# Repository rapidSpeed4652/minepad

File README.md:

# MinePad
Minepad is a 4 key macropad with a rotary encoder. It uses VIAL, which is a fork of QMK firmware.

(If it looks very green, try disabling the Edge.Cuts layer from the layers tab)

## Features
- 4 Cherry-MX keys
- 1 knob
- Support for mapping the keys and knob using VIAL

## CAD Model
It has two main parts and 8 small parts making the title and the logo. Made in Onshape!

## Schematic and PCB
Here's my schematic! Made in KiCAD.

PCB!

## Firmware
I have used VIAL, a fork of QMK firmware, to make it possible to map keys using a web portal.
- Rotary encoder for volume
- One key for pause/play
- Another for mute

I will decide what I do with other keys later.

## BOM
Everything needed to make this macropad:
- 4x Cherry MX Switches
- 1x EC11 Rotary Encoder
- 4x 1u Keycaps
- 1x Seeed XIAO RP2040
- 1x Case (All printed parts)

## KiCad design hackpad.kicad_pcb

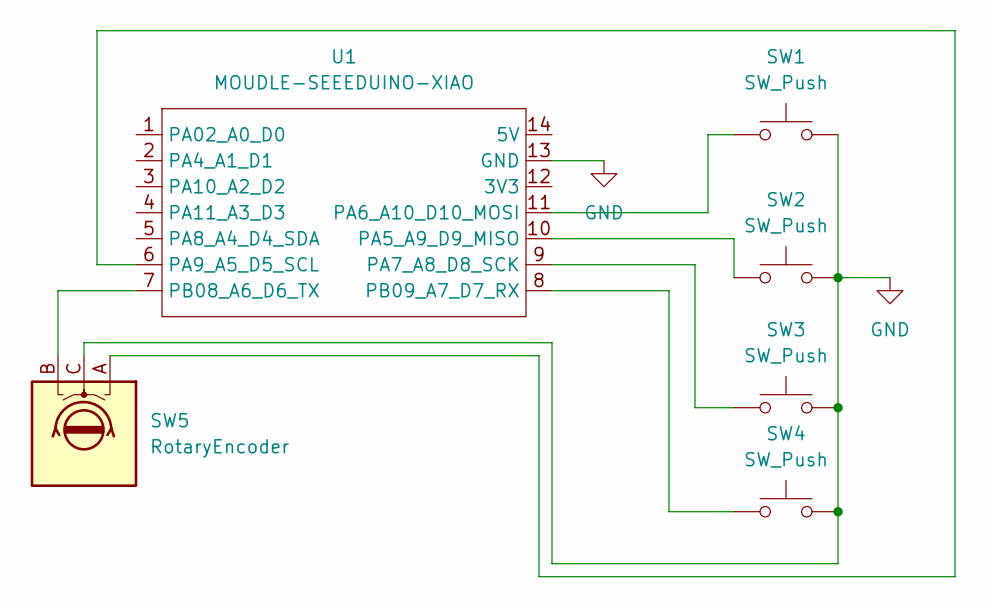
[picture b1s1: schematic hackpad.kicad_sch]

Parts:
SW1, SW2, SW3, SW4: SW_Push; SW_Cherry_MX_1.00u_PCB
SW5: RotaryEncoder; RotaryEncoder_Alps_EC12E-Switch_Vertical_H20mm
U1: MOUDLE-SEEEDUINO-XIAO; MCU_Seeed_ESP32C3

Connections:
GND: SW1.2, SW2.2, SW3.2, SW4.2, SW5.C, U1.13 (GND)
unnamed: SW2.1, U1.10 (PA5_A9_D9_MISO)
unnamed: SW1.1, U1.11 (PA6_A10_D10_MOSI)
unnamed: SW3.1, U1.9 (PA7_A8_D8_SCK)
unnamed: SW5.A, U1.6 (PA9_A5_D5_SCL)
unnamed: SW5.B, U1.7 (PB08_A6_D6_TX)
unnamed: SW4.1, U1.8 (PB09_A7_D7_RX)

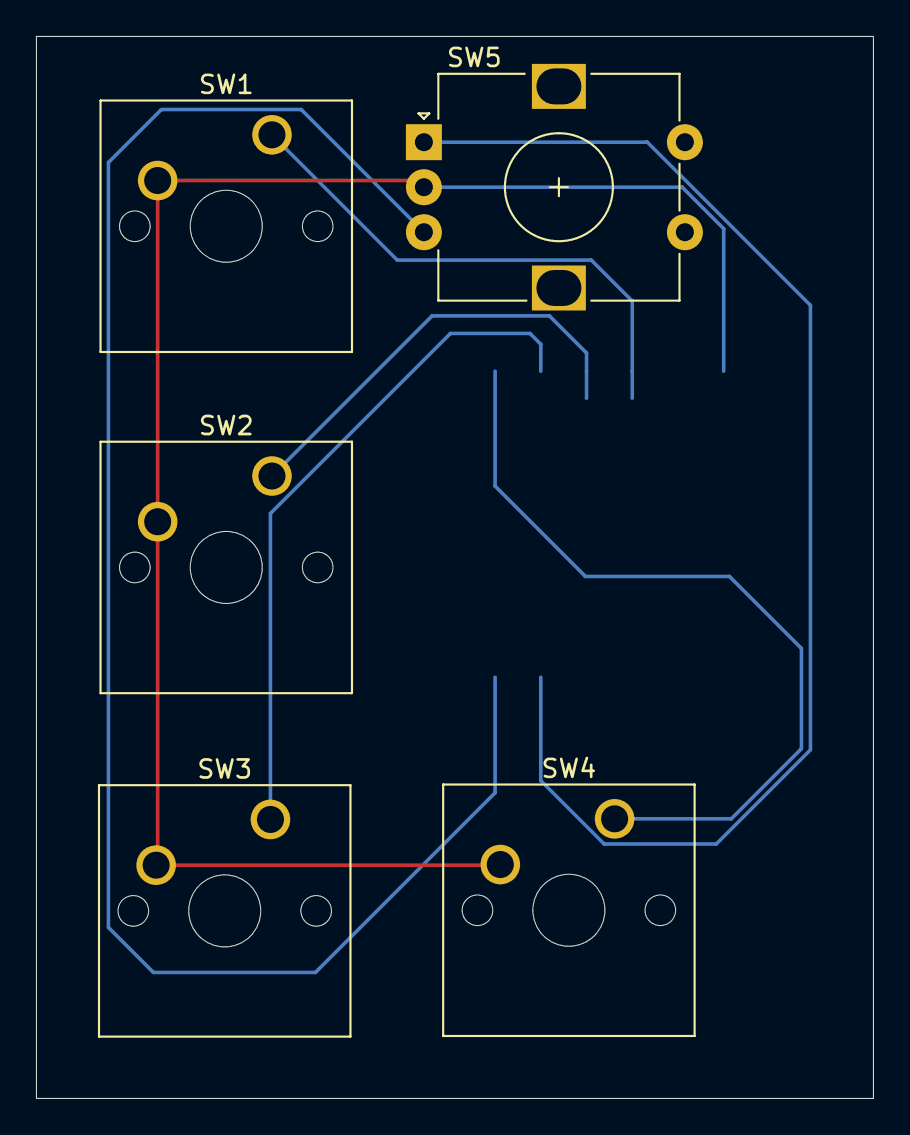
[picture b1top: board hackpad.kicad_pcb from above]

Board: 2 copper layers, 46.5 x 59.0 mm, 6 parts (1 on the bottom side), 7 nets.
